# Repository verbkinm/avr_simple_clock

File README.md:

# avr_simple_clock
https://cxem.net/mc/mc474.php

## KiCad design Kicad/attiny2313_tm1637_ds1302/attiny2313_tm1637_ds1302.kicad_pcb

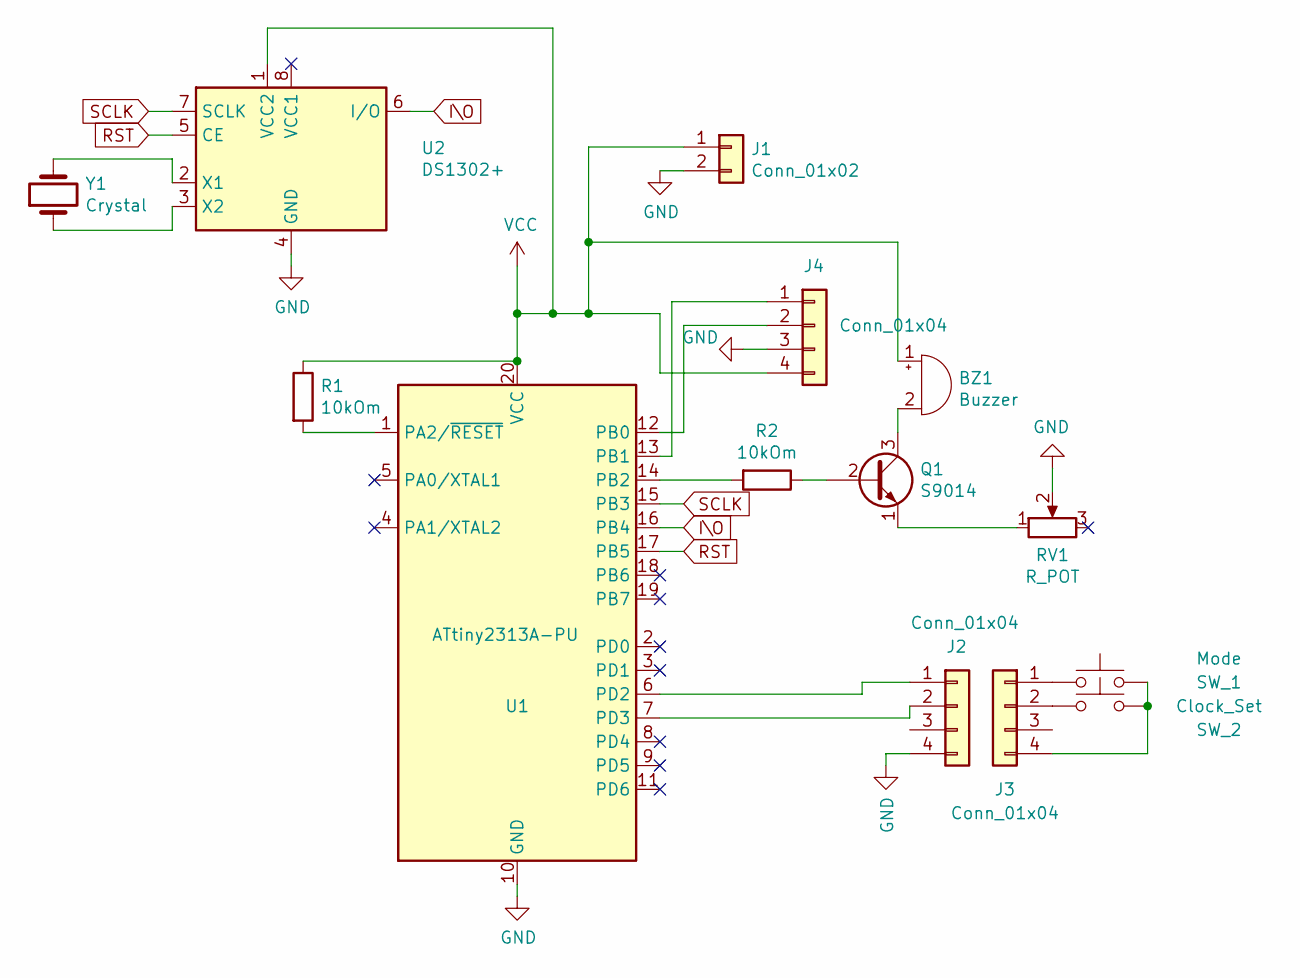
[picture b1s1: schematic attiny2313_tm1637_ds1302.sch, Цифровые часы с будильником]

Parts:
BZ1: Buzzer; Buzzer_12x9.5RM7.6
J1: Conn_01x02; power_pins_smd
J2, J3, J4: Conn_01x04; conn_01x04
Q1: S9014; TO-92_Inline
R1, R2: 10kOm; R_Axial_DIN0204_L3.6mm_D1.6mm_P5.08mm_Horizontal
RV1: R_POT; Potentiometer_Bourns_3386P_Vertical
SW_1: Mode; SW_PUSH_6mm
SW_2: Clock_Set; SW_PUSH_6mm
U1: ATtiny2313A-PU; DIP-20_W7.62mm
U2: DS1302+; DIP-8_W7.62mm
Y1: Crystal; Crystal_C26-LF_D2.1mm_L6.5mm_Horizontal

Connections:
GND: J1.2, J2.4, J4.3, RV1.2, U1.10 (GND), U2.4 (GND)
I\O: U1.16 (PB4), U2.6 (I/O)
unnamed: BZ1.1 (-), J1.1, J4.4, R1.1, U1.20 (VCC), U2.1 (VCC2)
unnamed: BZ1.2 (+), Q1.3 (C)
unnamed: J2.1, U1.6 (PD2)
unnamed: J2.2, U1.7 (PD3)
unnamed: J3.1, SW_1.1
unnamed: J3.2, SW_2.1
unnamed: J3.4, SW_1.2, SW_2.2
unnamed: J4.1, U1.13 (PB1)
unnamed: J4.2, U1.12 (PB0)
unnamed: Q1.1 (E), RV1.1
unnamed: Q1.2 (B), R2.1
unnamed: R1.2, U1.1 (PA2/~RESET)
unnamed: R2.2, U1.14 (PB2)
unnamed: U2.2 (X1), Y1.2
unnamed: U2.3 (X2), Y1.1
RST: U1.17 (PB5), U2.5 (CE)
SCLK: U1.15 (PB3), U2.7 (SCLK)

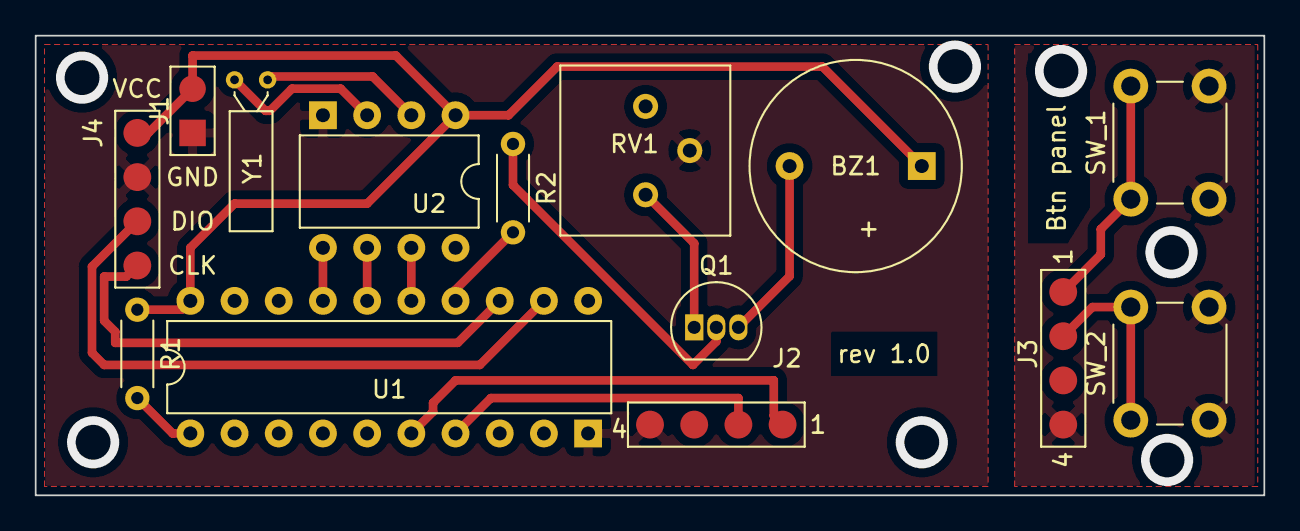
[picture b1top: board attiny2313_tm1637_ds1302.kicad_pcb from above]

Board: 2 copper layers, 70.6 x 26.4 mm, 14 parts (0 on the bottom side), 19 nets.

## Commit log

2020-07-14 first
2020-07-16 1.1 (cseg - 1436 Б, dseg - 24 Б)
2020-07-17 1.2 (cseg - 1382Б, dseg - 24 Б)
2020-07-17 Proteus - 1.0. Atmle studio - 1.2 (cseg - 1382, dseg - 24).
2020-07-17 Proteus - 1.0, Atmle studio - 1.2 (cseg - 1382, dseg - 24), datasheets
2020-07-21 add C version
2020-07-25 Proteus - 1.1, Atmle studio - 1.3 (cseg - 1472, dseg - 20)
2020-07-31 Proteus - 1.1, Atmle studio - 1.4 (cseg - 1556, dseg - 20) - Работает на макетной платеgit log!
2020-08-06 текстирование idle режима, работа на понижением энергопотребления
2020-08-13 Proteus - 1.3, Atmle studio - 1.5 (cseg - 2044, dseg - 29) - Будильник!
2020-08-14 время будильника хранится в eeprom
2020-08-15 уже почти
2020-08-15 уже почти 2
2020-08-16 PCB start
2020-08-18 fix BYTE number register
2020-08-18 created PCB
2020-08-19 не работает время
2020-10-12 убрана регулировка яркости, убрана кнопка яркости
2021-07-05 Питание от сети, не учитывать экономию батареи. Регулировка яркости (mode_9). Запись в eeprom данных будильника и яркости.
2021-07-05 Питание от сети, не учитывать экономию батареи. Регулировка яркости (mode_9). Запись в eeprom данных будильника и яркости. Убран сброс секунд после включения устройства.
2021-07-06 Убран режим сна. оставлен один тайме tim1. tim0 только на будильник(0C1A). Добавлена анимация при включении.
2021-07-06 gitignore
2021-07-06 ignore
2021-07-06 При любом режиме mode кроме mode_0 происходит сброс на режим mode_0 через ~60 сек. Для того чтобы выключался будильник и часы не оставались постоянно в режимах настройки, а сбрасывались на нормальный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
2021-07-06 Разбивка на файлы
2021-07-07 Корректировка моргания при переключении режимов
